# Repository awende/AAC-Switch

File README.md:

# AAC Switches

For more information, check out the blog post for the project [here](https://www.sparkfun.com/news/2452).

Repository Contents
-------------------

* **/Proximity Switch** - All Eagle design files (.sch, .brd, .png)
* **/Bluetooth Bridge** - Schematic and Arduino Code (.png, .ino)

License Information
-------------------
The hardware is released under [Creative Commons ShareAlike 4.0 International](https://creativecommons.org/licenses/by-sa/4.0/).
The code is beerware; if you see me at the local, and you've found our designs helpful, please buy us a round!

Distributed as-is; no warranty is given.

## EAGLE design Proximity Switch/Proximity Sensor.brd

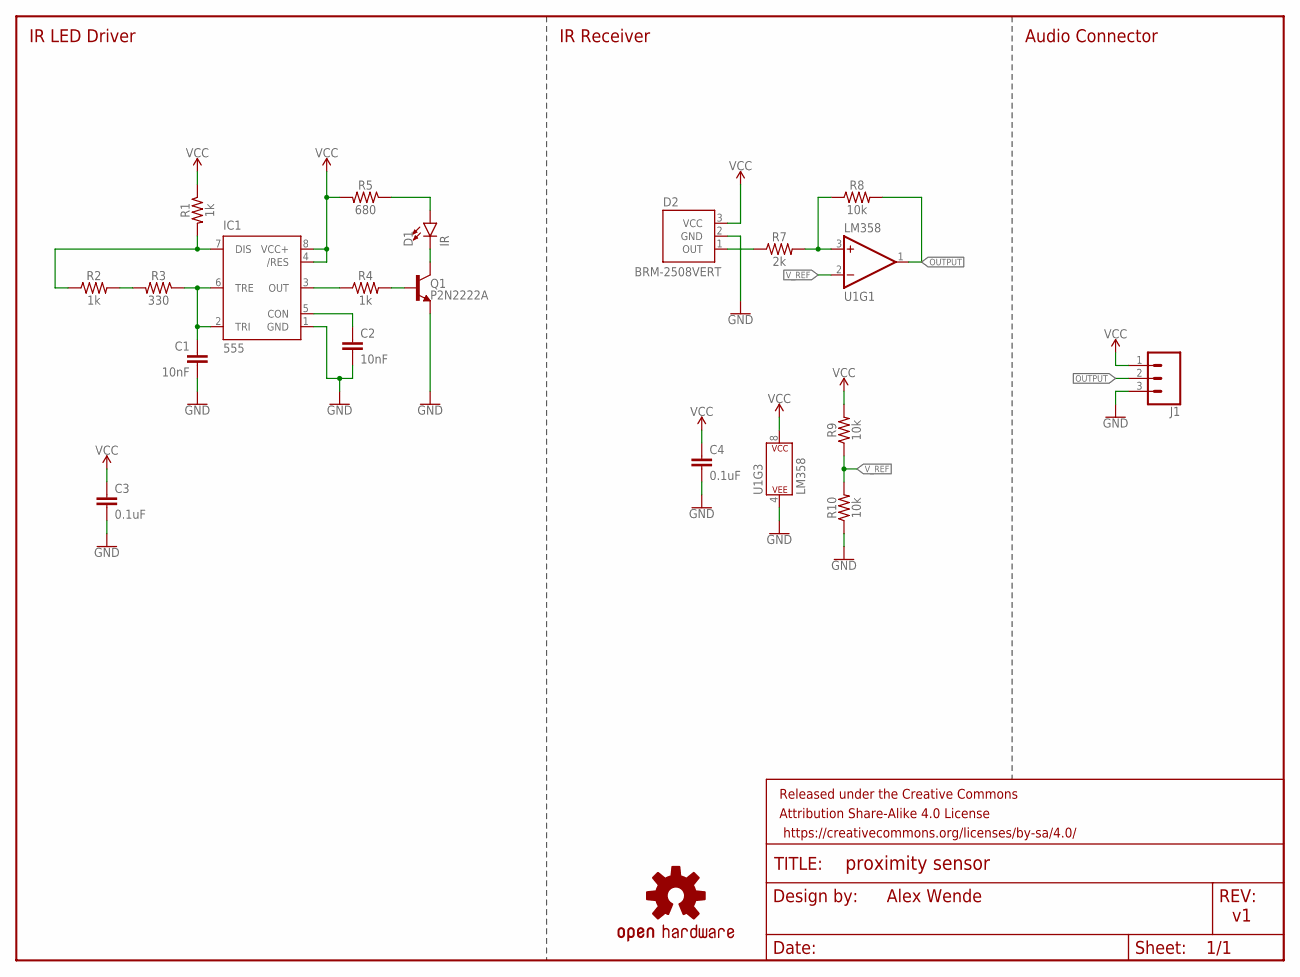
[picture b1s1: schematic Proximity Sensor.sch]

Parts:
C1, C2: 10nF; CAP-PTH-10MM
C3, C4: 0.1uF; CAP-PTH-SMALL-KIT
D1: IR; LED_5MM-KIT
D2: BRM-2508VERT; BRM-2508_VERT
FRAME1: FRAME-LETTERNO_PACKAGE; DUMMY
IC1: 555; DIP08-KIT
J1: CONN_03LONGPADS; 1X03_LONGPADS
LOGO1: OSHW-LOGOM; OSHW-LOGO-M
Q1: P2N2222A; TO-92
R1, R2, R4: 1k; AXIAL-0.3-KIT
R3: 330; AXIAL-0.3-KIT
R5: 680; AXIAL-0.3-KIT
R7: 2k; AXIAL-0.3-KIT
R8, R9, R10: 10k; AXIAL-0.3-KIT
U1: LM358; DIP08-KIT

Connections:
GND: C1.2, C2.2, C3.2, C4.2, D2.2 (GND), IC1.1 (GND), J1.3, Q1.3 (E), R10.P$1 (1), U1.4 (P$V-)
unnamed: C1.1, IC1.2 (TRI), IC1.6 (TRE), R3.P$1 (1)
unnamed: IC1.7 (DIS), R1.P$2 (2), R2.P$1 (1)
unnamed: C2.1, IC1.5 (CON)
unnamed: R2.P$2 (2), R3.P$2 (2)
unnamed: Q1.2 (B), R4.P$2 (2)
unnamed: IC1.3 (OUT), R4.P$1 (1)
unnamed: D1.A, R5.P$1 (1)
unnamed: D1.K (C), Q1.1 (C)
unnamed: R7.P$2 (2), R8.P$1 (1), U1.3 (+IN)
unnamed: D2.1 (OUT), R7.P$1 (1)
OUTPUT: J1.2, R8.P$2 (2), U1.1 (OUT)
VCC: C3.1, C4.1, D2.3 (VCC), IC1.4 (/RES), IC1.8 (VCC+), J1.1, R1.P$1 (1), R5.P$2 (2), R9.P$2 (2), U1.8 (P$V+)
V_REF: R9.P$1 (1), R10.P$2 (2), U1.2 (-IN)

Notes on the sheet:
Alex Wende
IR LED Driver
IR Receiver
Audio Connector

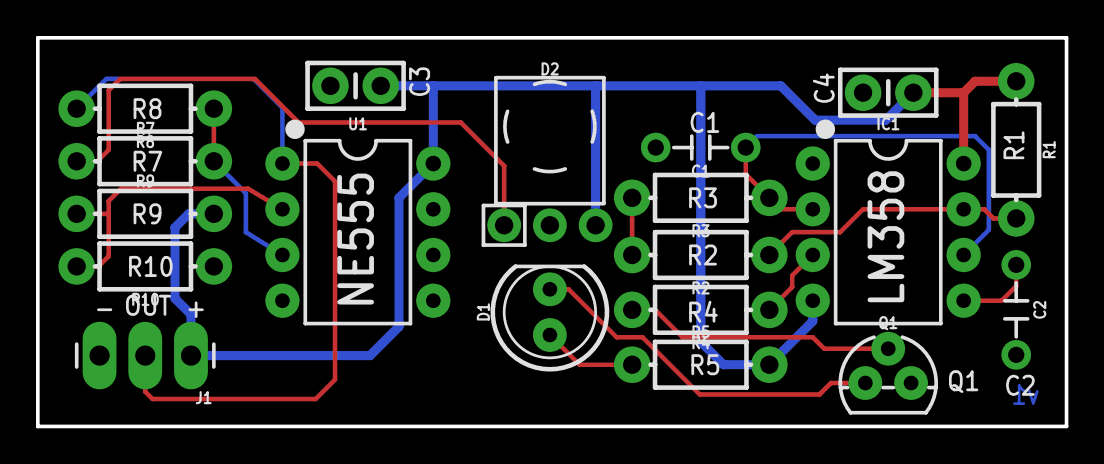
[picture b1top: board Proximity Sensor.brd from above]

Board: 2 copper layers, 57.1 x 21.6 mm, 21 parts (1 on the bottom side), 14 nets.

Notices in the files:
parts and their libraries:
SparkFun-Capacitors: Licensing: Creative Commons ShareAlike 4.0 International - https://creativecommons.org/licenses/by-sa/4.0
SparkFun-Aesthetics: Released under the Creative Commons Attribution Share-Alike 4.0 License
SparkFun-Aesthetics: Released under the Creative Commons
